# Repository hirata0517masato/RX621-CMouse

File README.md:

# RX621-CMouse
個人のバックアップ目的

マイコン：RX621

用途：クラシックマウス用

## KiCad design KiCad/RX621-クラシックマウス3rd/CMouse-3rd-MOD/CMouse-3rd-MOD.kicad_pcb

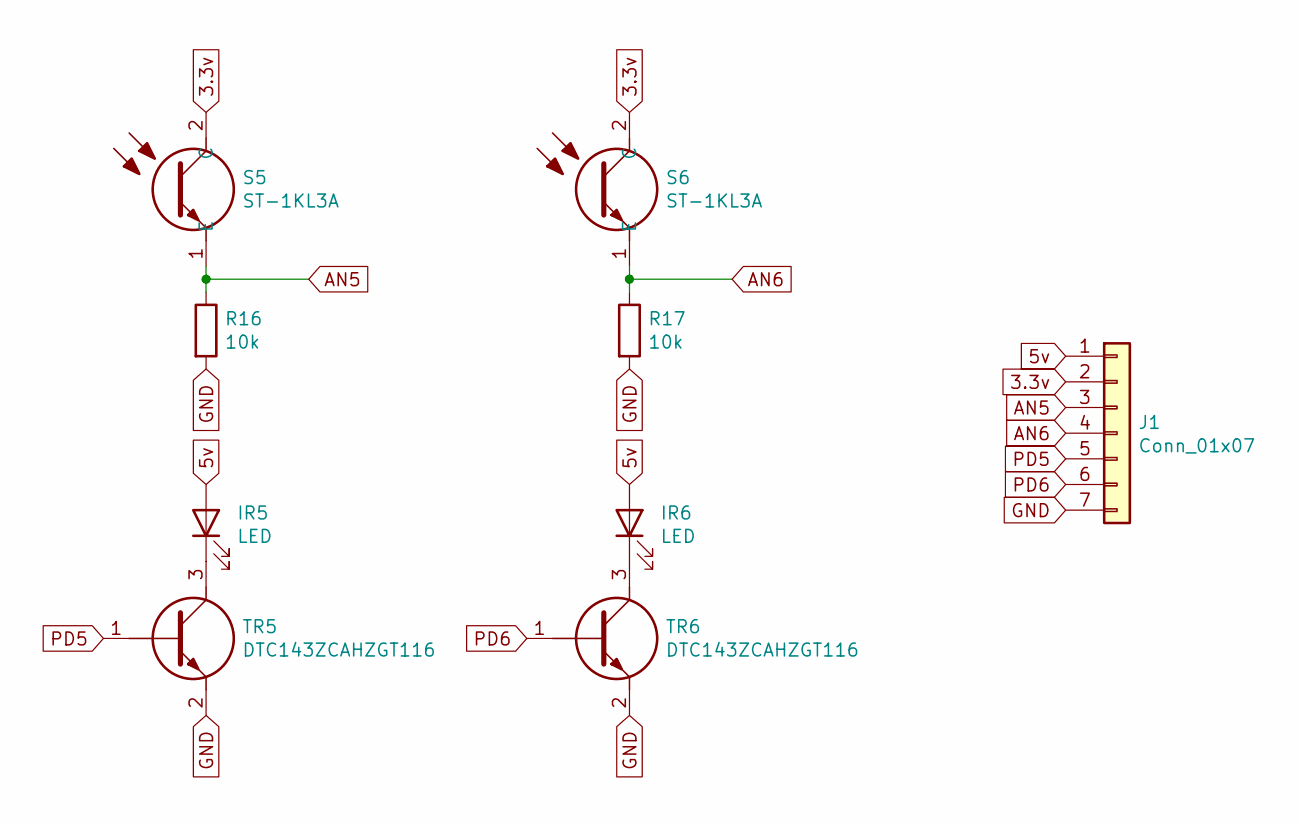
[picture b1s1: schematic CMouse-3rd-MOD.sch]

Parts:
IR5, IR6: LED; LED_D5.0mm
J1: Conn_01x07; PinHeader_1x07_P2.54mm_Vertical
R16, R17: 10k; R_0805_2012Metric_Pad1.15x1.40mm_HandSolder
S5, S6: ST-1KL3A; ST1KL3A; Manufacturer_Part_Number ST-1KL3A
TR5, TR6: DTC143ZCAHZGT116; SOT95P240X120-3N; Manufacturer_Part_Number DTC143ZCAHZGT116

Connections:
3.3v: J1.2, S5.2 (C), S6.2 (C)
5v: IR5.2 (A), IR6.2 (A), J1.1
AN5: J1.3, R16.1, S5.1 (E)
AN6: J1.4, R17.1, S6.1 (E)
GND: J1.7, R16.2, R17.2, TR5.2, TR6.2
unnamed: IR5.1 (K), TR5.3
unnamed: IR6.1 (K), TR6.3
PD5: J1.5, TR5.1
PD6: J1.6, TR6.1

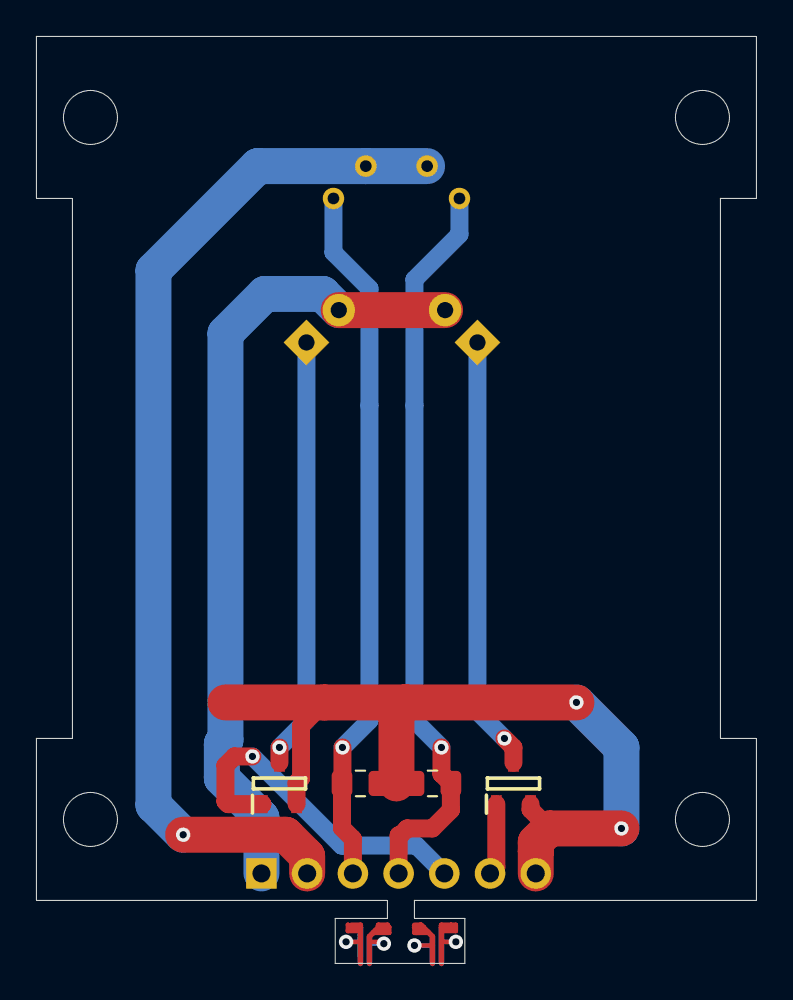
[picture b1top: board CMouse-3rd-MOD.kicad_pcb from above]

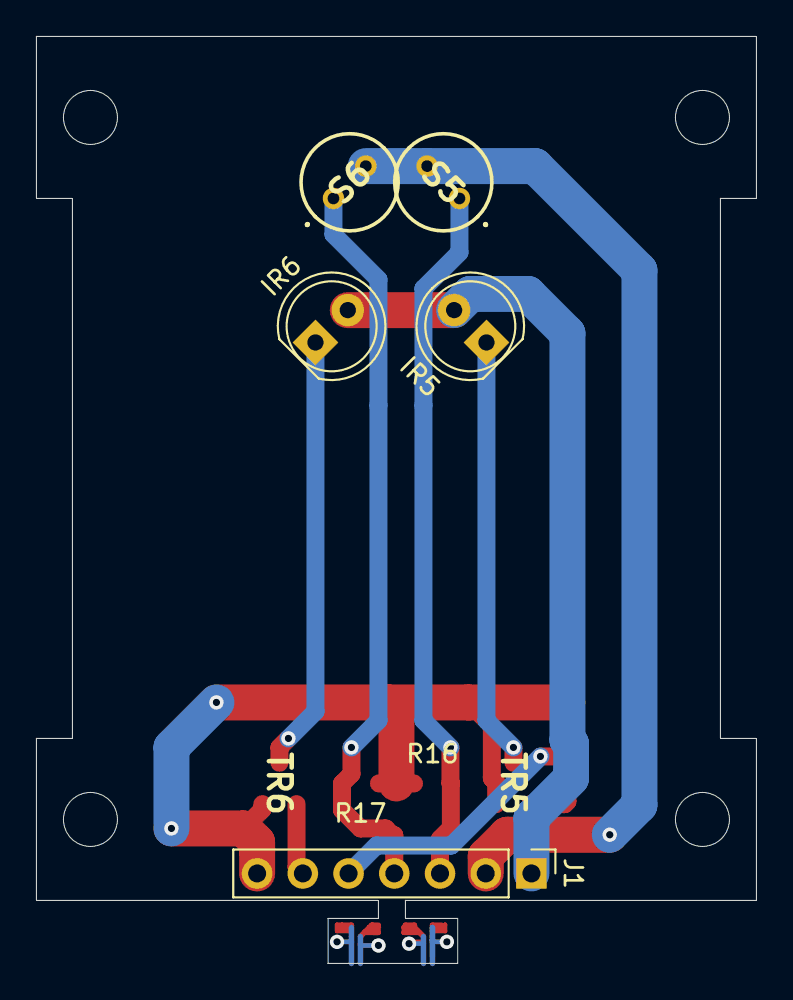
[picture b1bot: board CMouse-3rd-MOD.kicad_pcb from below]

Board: 2 copper layers, 40.0 x 51.5 mm, 9 parts (5 on the bottom side), 9 nets.

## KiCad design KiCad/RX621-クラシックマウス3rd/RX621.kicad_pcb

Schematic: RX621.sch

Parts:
BAT1: Conn_01x02; PinHeader_1x02_P2.54mm_Vertical
C1, C2, C4, C5, C6, C7, C8, C9, C10, C11, C12: 0.1u; C_0805_2012Metric_Pad1.15x1.40mm_HandSolder
C3, C13: 10u/6.3v; C_0805_2012Metric_Pad1.15x1.40mm_HandSolder
CN1: Conn_01x03; PinHeader_1x03_P2.54mm_Vertical
ENC_L1: Conn_01x04; PinHeader_1x04_P2.54mm_Vertical
ENC_R1: Conn_01x04; PinHeader_1x04_P2.54mm_Vertical
G1: Gyro1; PinHeader_1x05_P2.54mm_Vertical
G2: Gyro2; PinHeader_1x05_P2.54mm_Vertical
IC1: R5F56218BDFP#V0; QFP50P1600X1600X170-100N; Manufacturer_Part_Number R5F56218BDFP#V0
IC2: NJM7805SDL1-TE1; NJM7805SDL1TE1; Manufacturer_Part_Number NJM7805SDL1-TE1
IC3: TAR5SB33_TE85L,F_; SOT95P275X140-5N; Manufacturer_Part_Number TAR5SB33(TE85L,F)
IR0, IR1, IR2, IR3, IR4: LED; LED_D5.0mm
L1, L2, L3, L4: LED; LED_0805_2012Metric_Pad1.15x1.40mm_HandSolder
MD1: MotorD1; PinHeader_1x06_P2.54mm_Vertical
MD2: MotorD2; PinHeader_1x06_P2.54mm_Vertical
M_L1: Conn_01x02; PinHeader_1x02_P2.54mm_Vertical
M_R1: Conn_01x02; PinHeader_1x02_P2.54mm_Vertical
R1, R2: 4.7k; R_0805_2012Metric_Pad1.15x1.40mm_HandSolder
R3, R4, R5, R6: 10k; R_0805_2012Metric_Pad1.15x1.40mm_HandSolder
R7, R8, R9, R10: 1k; R_0805_2012Metric_Pad1.15x1.40mm_HandSolder
R11, R12, R13, R14, R15: 20k; R_0805_2012Metric_Pad1.15x1.40mm_HandSolder
S0, S1, S2, S3, S4: ST-1KL3A; ST1KL3A; Manufacturer_Part_Number ST-1KL3A
SW1: MODE_SW; PinHeader_1x03_P2.54mm_Vertical
SW2: TVAF06-A020B-R; TVAF06A020BR; Manufacturer_Part_Number TVAF06-A020B-R
SW3: SW_Push; TVAF06A020BR
SW4: POW_SW; PinHeader_1x03_P2.54mm_Vertical
TR0, TR1, TR2, TR3, TR4: DTC143ZCAHZGT116; SOT95P240X120-3N; Manufacturer_Part_Number DTC143ZCAHZGT116
X1: FC-255_32.768khz; FC255320000KAA0; Manufacturer_Part_Number FC-255 32.0000KA-A0
X2: CSTCE_12Mhz; CSTCE12M0G52AR0; Manufacturer_Part_Number CSTCE12M0G52A-R0

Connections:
+3.3V: C1.1, C2.1, C3.1, C6.2, C8.2, ENC_L1.1, ENC_R1.1, G1.1, G1.2, IC1.1, IC1.7, IC1.14, IC1.29, IC1.35, IC1.60, IC1.96, IC1.97, IC3.5, R4.1, R5.1, R6.1, S0.2 (C), S1.2 (C), S2.2 (C), S3.2 (C), S4.2 (C)
+5V: C4.1, C12.2, C13.2, IC2.3, IC3.1, IC3.3, IR0.2 (A), IR1.2 (A), IR2.2 (A), IR3.2 (A), IR4.2 (A), R1.1, R2.1
+BAT: BAT1.1, MD2.3, SW4.1
AN0: IC1.95, R11.1, S0.1 (E)
AN1: IC1.93, R12.1, S1.1 (E)
AN2: IC1.92, R13.1, S2.1 (E)
AN3: IC1.91, R14.1, S3.1 (E)
AN4: IC1.90, R15.1, S4.1 (E)
EMLE: IC1.2, R3.2
EXTAL: IC1.13, X2.3
GND: BAT1.2, C1.2, C2.2, C3.2, C4.2, C5.2, C6.1, C7.1, C8.1, C9.2, C10.2, C11.1, C12.1, C13.1, CN1.3, ENC_L1.4, ENC_R1.4, G2.5, IC1.3, IC1.4, IC1.12, IC1.15, IC1.31, IC1.38, IC1.62, IC1.94, IC1.99, IC2.2, IC3.2, MD2.4, R3.1, R7.2, R8.2, R9.2, R10.2, R11.2, R12.2, R13.2, R14.2, R15.2, SW1.1, SW3.1, TR0.2, TR1.2, TR2.2, TR3.2, TR4.2, X2.2
MD1: IC1.6, R5.2, SW1.2
unnamed: C5.1, IC3.4
unnamed: C7.2, IC1.5
unnamed: C11.2, IC2.1, SW4.2
unnamed: IR0.1 (K), TR0.3
unnamed: IR1.1 (K), TR1.3
unnamed: IR2.1 (K), TR2.3
unnamed: IR3.1 (K), TR3.3
unnamed: IR4.1 (K), TR4.3
unnamed: L1.1 (K), R7.1
unnamed: L2.1 (K), R8.1
unnamed: L3.1 (K), R9.1
unnamed: L4.1 (K), R10.1
P14: IC1.32, MD2.5
P20: IC1.28, MD2.2
P24: IC1.24, MD2.6
P34: IC1.16, MD2.1
PA0: IC1.70, L1.2 (A)
PA1: IC1.69, L2.2 (A)
PA2: IC1.68, L3.2 (A)
PA3: IC1.67, L4.2 (A)
PA4: IC1.66, R6.2, SW3.2
PB2: ENC_R1.2, IC1.58
PB3: ENC_R1.3, IC1.57
PB4: ENC_L1.2, IC1.56
PB5: ENC_L1.3, IC1.55
PD0: IC1.86, TR0.1
PD1: IC1.85, TR1.1
PD2: IC1.84, TR2.1
PD3: IC1.83, TR3.1
PD4: IC1.82, TR4.1
PE4: G2.1, IC1.74
PE5: G1.3, IC1.73
PE6: G1.4, IC1.72
PE7: G1.5, IC1.71
PWM_L1: MD1.2
PWM_L2: MD1.3
PWM_R1: MD1.4
PWM_R2: MD1.5
RST: IC1.10, R4.2
RxD1: CN1.2, IC1.20, R2.2
TxD1: CN1.1, IC1.22, R1.2
XCIN: C9.1, IC1.8, X1.1
XCOUT: C10.1, IC1.9, X1.2
XTAL: IC1.11, X2.1

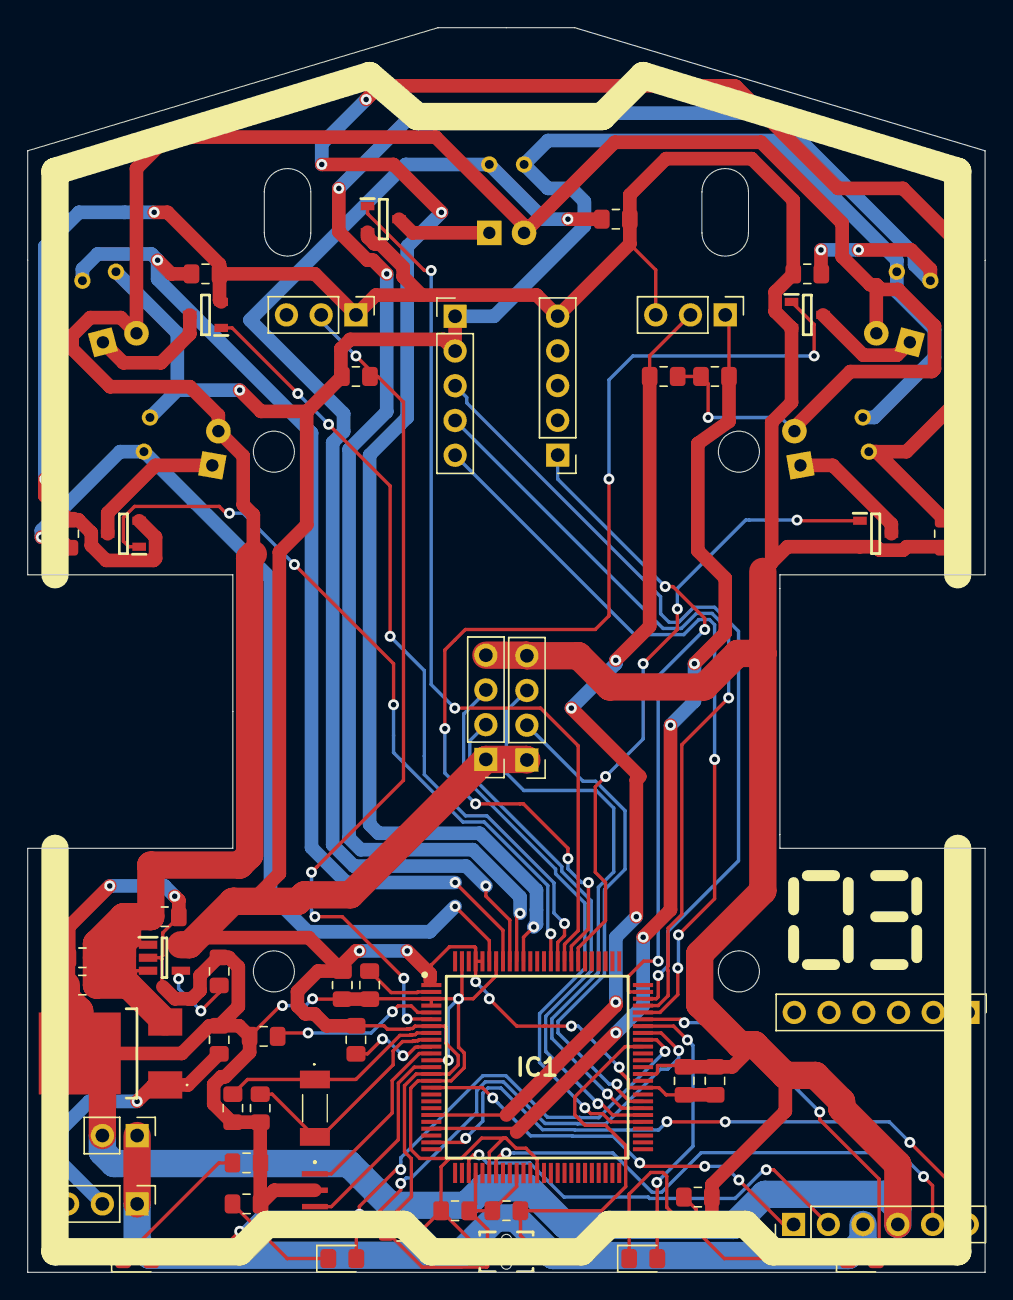
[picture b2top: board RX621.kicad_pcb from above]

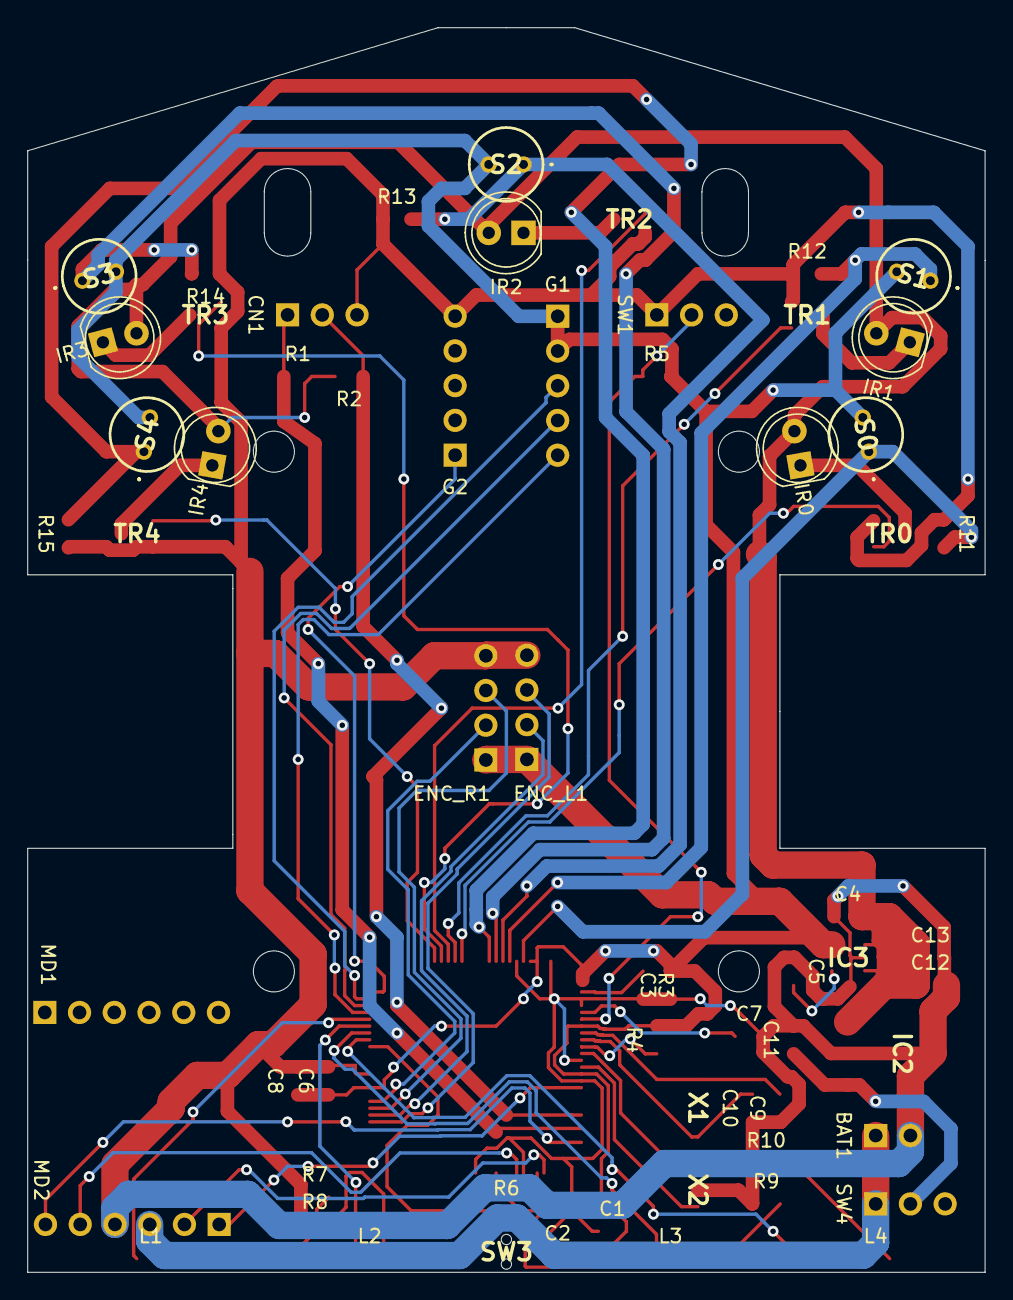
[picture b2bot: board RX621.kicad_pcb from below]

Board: 2 copper layers, 70.0 x 91.0 mm, 63 parts (10 on the bottom side), 52 nets.

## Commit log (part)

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2022-06-01 farst-comit
    動作確認中
2022-06-12 copy
    旧機種のプログラムを移植
    ビルドOK
    動作未確認
    パラメータ調整未実施
2022-06-16 Encoder_BugFix
    エンコーダ値のバグ修正
    ・基準値がマイナスの場合数値が異常であった
    ・レジスタ値がオーバーフローした際に値もオーバーフローしていた
2022-06-17 tuning
    ジャイロ、エンコーダの調整
    180mm前進の動作確認OK
    1mm=4パルスくらい
2022-06-19 first_run
    とりあえず走った
2022-06-23 maze_save
    迷路情報の保存を追加
    走行モードの追加
2022-06-24 tweak
    パラメータ調整
2022-06-25 tweak
    パラメータ調整
    直線速度UP、スラローム安定性UP
    最短走行時の初回加速の安定化
2022-07-01 debug_encoder
    長距離走行した場合エンコーダの値が異常になる問題を修正
2022-07-01 update
    迷路探索時に直進は１マスづつ進まずに進み続けるように変更
2022-07-03 super_update
    ・未確定区間の直線で壁切れを実装
    ・直線での加減速のアルゴリズムを見直し、安定する最高速度が向上
    ・センサー値の取得方法を更新（横壁の赤外線が前壁に影響する場合があった）
2022-07-06 naname
    斜め走行時の壁補正を個別にON,OFFできるように変更。
    今後、すべてのカーブを斜めにおきかえるのではなく、ジグザクのみ置き換える予定
2022-07-07 naname_update
    斜めの走行ルートを更新
    ４５度回転ではなくターンに変更
    Uターンorスラローム１回の時は斜めにしない
2022-07-07 bug_fix
    ビルドできない問題を修正
    余計な改行により不要なコードがコメントアウトできていなかった
2022-07-07 make_path_update
    探索時の最短経路作成アルゴリズムの改良
    ・未確定の直線のあとはルートを作成しないようにする
    未確定、未確定、確定、確定、、、のルートを作成した場合、１と２の間に壁が存在した場合でも確定ルートを走行してしまう。
2022-07-08 update
    壁切れによる距離補正
    最短走行時にも有効化
2022-07-09 bugfix
    最短走行時の壁切れは最終１マスのみに制限（以前と同様）
    修正：スラローム時の壁補正の向きが逆だった
2022-07-10 update
    ・最短走行時の壁切れ距離補正のパラメータを探索時と共通化
    ・迷路情報は上書きできるように変更（過去の情報より現在のセンサー値を優先）
2022-07-10 debug
    ・斜め走行パターンに変更するアルゴリズムの修正
    ・その他パラメータ調整
2022-07-11 update
    ・壁切れのアルゴリズムを改善
    ・パラメータ調整
2022-07-13 maze_all_search
    最短経路上の未確定マスをゴールと見立てて探索しに行くモードを追加
2022-07-15 safe
    ・一時的に最短走行の速度を調整できる機能を追加
    ・ゴール後、手が届きそうな場所まで戻ってくる機能を追加
2022-07-15 update
    パラメータ調整など
2022-07-15 update
    壁切れによる距離補正はミスが多いので無効化
2022-07-16 kansai2022-sisou
    関西2022試走でのソフト
2022-07-18 motor_update
    モータの制御周期を低くした。キーンという異音がなくなった。
2022-10-01 update
    タイヤのグリップ向上によるパラメータの更新
    探索時の既知区間加速の減速時のがたつきを軽減
2023-01-04 Timer
    タイム計測機のソフト
2023-01-14 debug
    高速時のバタつきを修正
    高速時の壁補正の上限を追加
2023-01-21 big_update
    ログ機能を実装
    センサーの個体差を微調整
    斜め走行の安定化など
2023-01-21 debug
    ログ初期化時に迷路情報まで削除していた問題を修正
2023-01-22 update
    ・壁の距離補正、近すぎる場合の補正量を増加
    ・センサー値の微修正
2023-01-25 new_Mouse
    センサー値が不安定になったため、機体を作り直した。なのでソフト微修正。
2023-01-26 speed_up
    斜め無しでの最短走行の安定性、速度UP
2023-01-27 update
    速度向上、安定感UP
2023-01-29 IR_0.25ms
    蛍光灯のちらつき対策
    赤外線センサーのON,OFFの時間差を少なくすることでちらつきによる影響を軽減
2023-01-31 reset
    タイマーのリセット機能を追加
2023-01-31 reset_debug
    デバッグ
2023-02-02 update
    パラメータ調整
2023-02-06 update
    なんかいろいろ変更
    センサー取得割り込みの優先度を上げる
    各種パラメータ調整
    最短経路上の未確定マスを探索するアルゴの修正
    迷路情報を保存していないときは片道で自動保存
    など
2023-02-17 update
    モード追加
    ９０度旋回の重みを調整できるようになった
    など
2023-06-13 3rd-first
    3号機用データを作成中
2023-06-18 3rd_run
    ３号機の探索、最短走行の確認が完了
    これで２号機からの移植は完了とする
2023-06-20 update
    斜め調整開始
2023-07-01 maze_update
    迷路情報を間違って記録している可能性があるときは再チェックできるようなった
2023-07-01 Gyro_init
    ジャイロ初期化タイミングを変更
    初回走行前に実施することで、起動時の初期化動作が不要になる。ただし、初回走行時の走行開始待ち時間が伸びる
2023-07-01 update
    パラメータの更新
    斜め2マスの時の壁切れ安定化（少し進んでから壁切れチェックした方が良い）
2023-07-02 debug
    経路導出を改善
    距離が同じときは斜めを優先する
2023-07-02 update
    前壁が近いすぎるときはモータの出力（前進）は半分にする
2023-07-11 update
    パラメータ調整
    スタート時、左右の壁に寄っていた場合LEDに表示する機能を追加
2023-07-17 kansai2023
    関西２０２３の設定
2023-07-27 wall
    壁制御のアルゴリズムを変更
2023-08-15 update
    パラメータ調整
    軽微なバグ修正
2023-09-12 update
    タイヤが消耗していたので交換した
    のでパラメータ調整
2023-09-17 update
    パラメータ調整
    速度を上げたほうが制御の雑さが薄まる気がする
2023-09-18 update
    パラメータ調整
    斜め壁切れ判定の変更
2023-10-16 U
    Uターンを追加
2023-10-21 update
    16x16での調整を実施
2023-10-29 update
    パラメータ調整
    未知区間加速を追加
2023-10-29 update
    パラメータ更新
2023-11-04 update
    ギア比変更によるパラメータ調整
    前8:40 今10:38
    エンコーダ処理の改善
    エンコーダ距離計測時に同処理が割り込みで再度呼び出される可能性の対応
2023-11-24 update
    ・ギア比を戻した（安定性を優先）
    ・ジャイロの不要な軸は読み込まない（余分なSPI通信をなくす）
    ・斜めの最初の１マスは壁補正無し
    ・スラロームでの前壁補正を追加
    ・直進の加速度をいろいろ変更
    ・パラメータ調整
2023-11-24 debug
    斜めの前壁距離補正の前に斜め用のジャイロ設定をしていた問題を修正
2023-11-25 update
    高速時に直線距離がずれる問題の対策
    ・距離の計測方法を左右の平均値から左右の最小値に変更
    最小値＝空転、ノイズが発生していない可能性が高い
2023-12-16 SensorADD
    斜め４５度センサーを増設
2023-12-17 BIG
    斜め45度センサーを使用した大曲を追加
2023-12-17 3rd-MOD
    斜め４５度センサー増設用データを追加
2023-12-17 45
    斜めの出るときを４５度センサーを使用するように変更
    メモ：Vターンが未完成
2023-12-20 update
    Vターンの調整
    左右のずれが大きいときは大曲禁止
    2マスのVターンが調整できていない
2024-01-08 naname_in
    直線から４５ターンを斜めセンサーを使用する壁切れに変更
2024-01-08 naname_kabe
    斜めセンサーのみ壁が見えているときの壁補正を追加
2024-01-08 time
    前壁補正は指定時間を経過すると強制終了するように変更。角度、距離がずれる可能性があるがスタックして動作不能になるよりマシと判断する。
2024-01-08 V2
    ２マスVターンの調整
2024-01-28 update
    パラメータ更新
    探索の壁補正はゲイン少な目、許容誤差少な目がいいかも？
2024-02-01 update
    安定性向上
2024-02-04 update
    練習会で調整後、苦手パターンを再度調整
2024-02-08 naname
    斜めを考慮した最短経路を求めるモード６を実装
    ただし、モード４の探索では斜めを考慮しないため斜めに必要なマスを探索しないことが課題
2024-02-12 naname
    斜め修正
    ジャイロ補正値の閾値は絶対値にすると切り返しが反応できない場合があるため、補正したい方向の最大値を超えていなければ補正できるように変更
2024-02-14 update
    斜めの壁補正を調整
    大曲の壁切れが距離が遠かった時の距離補正を追加
2024-02-15 kushi
    串対策の調整
    柱で微妙に壁補正をしてふらつくので閾値の調整
2024-02-16 update
    各種調整
2024-02-19 2023
    全日本2023のソフト
2024-05-02 update
    斜めの重みを微調整するモードを追加
2024-07-07 maze_ng_check
    迷路情報を保存するとき、最短走行前に最短経路が存在するか確認する機能を追加
2024-07-13 bugfix
    ゴールできない迷路の場合、保存しない処理のバグ修正版。迷路情報リセット時に保存できない状態だった
2024-07-14 check_full
    ・最短経路のある、なしチェック関数に未確定壁あり版、なし版の２つを作成
    ・走行モードの順番をいれかえ
2024-07-15 update
    最短経路上の未確定マスを探索する際に、ゴールできない迷路情報（探索ミス）が発生した場合は前回の情報に戻す機能を追加
2024-07-15 test
    斜めを考慮した最短経路上の未確定マスを探索するソフトを作成中。まだ意図した動作をしないのでコメントアウト状態
2024-07-27 kansai2024
    2024関西地区大会でのソフト
2024-07-28 update
    ・斜めを考慮した経路探索にて同じマスをループしないように修正
    ・探索走行にて、左右の壁が遠すぎる、近すぎる場合は回転し前壁補正を行うように変更
2024-07-28 update
    斜めを考慮した探索時に経路がループする可能性があったため、一度確認したマスは到達しないように修正
2024-10-20 update
    ・タイヤを新品に交換したのでパラメータ調整
    ・以下の機能を追加
    全面探索時の制限時間調整機能
    クラッシュ時に直前１５秒前の壁情報を保存する機能
    ログの可視化機能、かつ重み情報の出力
    全面探索時に制限時間に到達した場合はスタート地点ではなくピックアップ地点に戻る、かつ最適な最短経路が見つかっていない場合は４５度回転を行い視覚的に判別できる機能
2024-10-20 bug
    斜めを考慮した最短経路探索にゴール後に戻ってこれないバグあり。最短経路導出の際に無限ループしている様子。現状は使用しないようにする
2024-10-27 debug
    斜めを考慮した経路選択にて、周囲の重みが同じ場合にゴールできないマスを選択する可能性があった問題を修正。同じ重みを見つけた場合は単純な重み計算の小さいほうを優先するように変更。また、斜めを優先するためLRLRLR,,,の向きを計算していた式にも問題があったため修正。
2024-12-14 update
    ・探索時に壁切れで距離補正できないパターンがあったため修正
    ・斜めを考慮した経路探索にバグがあるため無効化。ゴール直後に正面壁に激突する。
2024-12-15 debug
    斜めを考慮した経路探索を実行した際、経路算出時に現在位置を変更してしまうバグを修正
2024-12-31 update
    ゴール座標を変更する機能を追加
2025-03-22 update
    ・前壁補正時に前左右のセンサー値の差分が大きいときは調整する機能を追加
    ・壁補正のパラメータ調整。弱めに設定することで急激なブレを軽減する
2025-04-19 update
    １本の柱に３つの壁無しが確定したとき、残りの１枚は壁が確定する処理を追加
2025-05-17 update
    最短経路上の未確定マスを探索する前に確定壁がないマスを探索し、余分な探索を削減する作戦（動作未確認）
2025-05-17 bugfix
    確定壁がないマスを探索する際に到達不可能のマスは対象外とする処理を追加
2025-07-19 update
    ・最短ゴール時に前壁だけでなく、左右の近いほうの壁と距離補正をするように変更
    ・パラメータ調整
    kdは高いほうが良いかも
2025-07-21 dijkstra
    ダイクストラを追加
2025-07-27 kansai2025
    関西2025のコード
2025-08-15 update
    ・ギア比を 8:40から10:38に変更
    ・Uターンを有効化
    ・パラメータ調整
2025-08-15 update
    探索での既知区間はスラロームするように変更
2025-08-16 update
    壁切れでの距離補正の発生個所を追加
2025-12-13 update
    ・直線の距離を補正するテーブルを追加
    ・パラメータ調整
    ・最短後のピックアップ位置までの移動は確定マスのみ使用する
2025-12-14 Silicon-tire
    タイヤ変更
    シリコンシート＋スポンジ
    幅12mm
2026-01-11 update
    探索：既知区間の直線が1マス後のスラロームが発動しない問題を修正
    タイヤ幅を15mmに変更したためパラメータ調整
2026-01-12 update
    ゴール入口が2か所の時対策を追加
    ・設定したゴール方角と異なる方角でゴールする可能性があったため、スタート前にゴール方角を変更する機能を追加（ダイクストラはまだ未対応）
2026-01-12 update
    ダイクストラ使用時、設定したゴール方角と異なる方角でゴールした場合に方角がずれる問題を修正
    経路作成時の向きでゴール方角を補正するように変更
2026-02-14 debug
    ・前壁激突の原因を改善
    未知区間の場合、前壁が近いのにまだ1マス進めると思って激突していた
    ・未知区間走行用の処理を通常の走行処理と同じアルゴリズムに統一
    滑りによる距離ずれが同じになった
    ・最終１マスの壁切れ時に半マス進むではなく、距離補正に変更
    不用意な加減速をなくす
2026-02-19 time
    探索の制限時間の計測開始をモード１にも追加
2026-02-23 2025
    全日本2025のコード
2026-04-18 update
    探索時の壁切れ補正を無効化
2026-04-26 mf50-2mm-12mm
    タイヤの変更
    mf-50 2mm厚 12mm幅に変更
    各種パラメータの調整
2026-05-04 update
    迷路の板を公式仕様に変更
    ・パラメータ調整
    ・最短のみkdを変更（ブレを少なくする）
2026-05-05 naname_update
    斜めの経路選択アルゴリズムを変更（修正）
    マップの重みが同じ場合は斜め方向を選択するように変更
2026-05-17 update
    探索時の壁補正を横センサーから斜め横センサー優先に変更
2026-05-17 update
    最短の壁補正を斜めセンサーを優先に変更
    ゲインは弱めに設定する
2026-05-17 kabe
    壁制御の調整
2026-06-06 update
    壁制御のパラメータ変更
    Uターンを斜めセンサーの壁切れに変更
2026-06-14 合宿2026
    合宿で調整したパラメータ
2026-06-15 update
    パラメータ調整
    直線の震え対策
    斜めセンサーが左右で値が異なっていたかも
2026-06-17 log
    ログにジャイロの値を追加
2026-06-20 update
    パラメータ調整
    直線距離が長いときにカーブで滑るので減速
2026-06-20 debug
    ３か所壁がなければ残りは壁無しが確定する処理が正常に動作していなかったため修正
2026-06-20 update
    最短の壁制御を斜めセンサーから横センサーに変更
    パラメータ調整
2026-06-28 search,enc
    ・全面探索時、既知区間のみで移動する。
    既知区間＝ほこりが少ない経路を使用する。
    迷路によっては振り回される可能性があるので注意
    ・壁切れの速度上限を追加
    壁切れチェック時にエンコーダの上限を超えている場合は減速するように改良
2026-06-28 kabegire
    壁切れの速度制御
    速度が遅いときに加速する処理を追加
2026-06-28 debug
    全面探索で時間切れの場合、取りやすいところで終了するはずが、1,1固定になっていたバグを修正。
    原因はピックアップ座標の更新忘れ
2026-06-30 log
    ログビューワ対応
    走行経路を可視化するツールを作成
